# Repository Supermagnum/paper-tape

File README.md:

# Paper Tape Reader

**Repository:** [github.com/Supermagnum/paper-tape](https://github.com/Supermagnum/paper-tape)

Design and documentation by [Jürgen Müller / e-basteln](https://e-basteln.de/computing/papertape/overview/). This repository contains the firmware, PCB design files, and manufacturing data for the manual optical paper tape reader described on the [e-basteln Paper Tape Reader pages](https://e-basteln.de/computing/papertape/overview/).

PCB files converted to KiCad. Note that the main board and included template PCBs use **1.6 mm** thickness. The Gerber files in `gerbers/papertape_spacer/` are for the **1.6 mm templates** (identifiable by their larger aperture holes), used as alignment guides during assembly.

The actual **spacers** (2× 1.2 mm thick) are **not included as Gerber files** and must be made separately. The main board and spacer templates also require **different PCB thicknesses** and must be ordered as **separate jobs** from your PCB manufacturer. Both 1.6 mm and 1.2 mm are standard thickness options at JLCPCB and PCBWay, with a minimum order of 5 pieces each.

The material of the spacers is not important, they just have to be light-tight. Options include 3D printing in black filament, or cutting from 1.2 mm black acrylic or similar opaque material. Use the 1.6 mm template PCB as a guide when making them. Make 2× spacers, for a total thickness of 2.4 mm.

## Table of Contents

- [Overview](#overview)
- [Using the Reader](#using-the-reader)
  - [Capturing tape data](#capturing-tape-data)
  - [After capture](#after-capture)
  - [Archiving captures on Codeberg](#archiving-captures-on-codeberg)
    - [Creating a Codeberg account](#creating-a-codeberg-account)
    - [Creating a repository](#creating-a-repository)
    - [Uploading files via the web interface](#uploading-files-via-the-web-interface)
- [LEDs](#leds)
- [Calibration](#calibration)
- [Jumpers](#jumpers)
- [Serial Output](#serial-output)
- [Building the Reader](#building-the-reader)
  - [Builder's Hints](#builders-hints)
    - [Sourcing the parts](#sourcing-the-parts)
    - [Preparing the PCBs](#preparing-the-pcbs)
    - [Populating components](#populating-components)
    - [Populating sockets and pins](#populating-sockets-and-pins)
    - [Programming the Pro Micro](#programming-the-pro-micro)
- [Design Approach](#design-approach)
- [The Sales Pitch](#the-sales-pitch)
- [Where to Find Files](#where-to-find-files)
- [Design Files](#design-files)
  - [Changes in this repository](#changes-in-this-repository)

## Overview

This little manual paper tape reader is easy to build and operate. It connects to any modern computer via USB, and performs well with all kinds of 5 to 8 bit paper tape, including translucent paper materials. To compensate for sensor tolerances and adjust to different paper types, it can automatically calibrate its optical sensors.

The paper tape reader is controlled by an Arduino Pro Micro. Punched holes are detected optically, via analog inputs to the Arduino and automatic thresholding in software.

Optical readers for punched paper tape have been used since the 1940s; the one developed in 1942 for the British Heath Robinson deciphering machine was probably among the earliest. Non-motorized optical readers, where the tape is pulled through by hand, became popular with early computer amateurs in the 1970s. Oliver Audio Engineering launched the OP80A as a kit or complete unit in 1976; a replica is still commercially available today. And to this day, amateurs interested in the old paper tape format occasionally build their own optical readers.

Operate the reader handheld or mounted to a base plate. Tape is pulled through manually, at up to 1 meter/second feed rate.

The two main modules are the phototransistor detector (left) and the LED illuminator (right). The Arduino sits on top of the detector module. Only two power connections go to the illuminator.

All chassis parts are made from PCB material: Circuit boards for phototransistors and LEDs, masks to precisely define the illumination and detection apertures, and light-tight spacers.

## Using the Reader

To use the paper tape reader, simply connect it to a Windows 10, Linux or Mac OS computer via USB. The reader should automatically register as a USB CDC device (communication device class, a virtual serial port).

Start a terminal program of your choice and select the right (virtual) serial port. No need to set the baud rate etc., since no physical serial port is involved. The reader will start sending data as soon as you pull paper tape through.

Before the first operation, or when switching to a new type of paper tape with very different transparency, calibrate the reader as described below.

### Capturing tape data

Open the serial port and save the received contents to a `.txt` file with **no processing**. Capture the raw bytes exactly as received, save as plain text, and do not strip or convert anything. This means:

- No parity bit masking
- No line ending conversion
- No stripping of leader/trailer nulls
- No interpretation of control characters

This preserves everything and keeps your options open for later analysis.

**Linux:** find the device (often `/dev/ttyACM0` or `/dev/ttyUSB0`), then capture directly:

```bash
stty -F /dev/ttyACM0 raw -echo
cat /dev/ttyACM0 > 20250627_tape_001.txt
```

Press Ctrl+C when the tape has passed through. Do not pipe through tools that alter line endings or encoding.

**macOS:** same approach using the device under `/dev/tty.usb*` or `/dev/cu.usb*`.

**Windows:** use a terminal that can log raw serial data to a file without translation (for example PuTTY with "All session output" logging, or a dedicated serial capture tool). Disable any "local echo", line editing, or automatic CR/LF conversion in the terminal settings.

A good naming convention helps since you do not know the content yet:

```
YYYYMMDD_tape_001.txt
```

If you are digitizing a collection, this lets you track what you have read and when, and rename files later once you figure out what each tape contains.

### After capture

Once you have a faithful raw capture, you can:

- Open it in a hex editor to inspect the raw bytes and identify the format
- Run `file tape_001.txt` on Linux, which will attempt to auto-detect the content type
- Look for recognizable patterns such as keywords (`PROGRAM`, `BEGIN`, `MOV`, `LDA`, etc.) that identify the language
- Check the [bitsavers.org](https://bitsavers.org/) archive, which has a large collection of documented paper tape formats for comparison

The key principle is: **capture first, identify later**. You can always convert a faithful raw capture, but you cannot recover data that was thrown away during capture.

### Archiving captures on Codeberg

If you want to share digitized tapes with the retrocomputing community, [Codeberg](https://codeberg.org/) is a good place to host them. Codeberg is independently operated by [Codeberg e.V.](https://codeberg.org/Codeberg/Association), a non-profit association registered in Berlin, Germany. It is community driven, privacy focused, and runs on the open-source [Forgejo](https://forgejo.org/) platform under German and EU law (GDPR). For archival work, that means no commercial pressure to monetize the platform, stronger data protection than many US-hosted services, and a community that tends to appreciate preservation projects.

#### Creating a Codeberg account

1. Open [codeberg.org](https://codeberg.org/) in your browser.
2. Click **Register** in the top-right corner.
3. Choose a username, enter your email address, and set a password.
4. Complete the registration form and submit it.
5. Check your email for a confirmation link from Codeberg and click it to activate the account.
6. Sign in with your new username and password.

#### Creating a repository

1. After signing in, click the **+** icon in the top-right corner and select **New Repository**.
   Alternatively, open your dashboard and click **New Repository** there.
2. Fill in the repository details:
   - **Owner:** your username (or an organization, if you belong to one)
   - **Repository name:** for example `paper-tape-archive`
   - **Description:** short summary, e.g. "Digitized paper tape captures"
   - **Visibility:** choose **Public** if you want others to browse and clone the archive
   - **Initialize repository:** leave **Add a README file** unchecked if you plan to upload your own files immediately; check it if you want Codeberg to create an empty starter `README.md` for you
3. Click **Create Repository**.

You now have an empty repository ready for uploads.

#### Uploading files via the web interface

Codeberg's web interface lets you add files without installing Git on your computer. This works well for small archives and individual tape captures.

**Upload the first files to an empty repository:**

1. Open your new repository in the browser.
2. If the repository is completely empty, Codeberg shows an **Upload file** option on the landing page. Click it.
   If the repository already has files, go to the **Code** tab, click the **+** drop-down next to the path bar, and choose **Upload file**.
3. Drag and drop files into the upload area, or click to browse your computer.
4. In the **Commit message** field, enter a short note such as `Add initial archive structure`.
5. Optionally expand **Commit options** and choose whether to commit directly to the default branch (usually `main`).
6. Click **Commit changes**.

**Add a tape capture in a subdirectory:**

1. Navigate to the folder where the tape should live, for example `tapes/unknown/20250627_tape_001/`.
   To create a new folder path, type the full path into the filename field when uploading, for example:
   `tapes/unknown/20250627_tape_001/tape_001.txt`
   Codeberg creates any missing directories automatically.
2. Upload the raw capture file (`tape_001.txt`) and the tape's `README.md` (create the README in the web editor if you prefer).
3. Enter a commit message such as `Add tape 001 capture from 2025-06-27`.
4. Click **Commit changes**.

**Create or edit a README in the browser:**

1. On the **Code** tab, click the **+** drop-down and choose **New file**.
2. Enter the path, for example `tapes/unknown/20250627_tape_001/README.md`.
3. Type or paste the README content into the editor.
4. Add a commit message and click **Commit changes**.

Repeat for each new tape. Once you have several captures, consider organizing them using the directory structure below.

Suggested directory structure:

```
paper-tape-archive/
├── README.md                    # Project description, how to contribute
├── FORMATS.md                   # Notes on identified tape formats
│
└── tapes/
    ├── unknown/                 # Tapes not yet identified
    │   └── 19700101_tape_001/
    │       ├── README.md        # Date, physical condition, likely source
    │       ├── tape_001.txt     # Raw capture
    │       └── tape_001.bin     # Raw binary if needed
    │
    ├── assembler/
    │   └── 19780315_tape_002/
    │       ├── README.md
    │       └── tape_002.txt
    │
    ├── basic/
    ├── fortran/
    ├── pascal/
    └── other/
```

Each tape's `README.md` should contain something like:

```markdown
# Tape 001

- **Date captured:** 2025-06-27
- **Capture device:** Paper Tape Reader (github.com/Supermagnum/paper-tape)
- **Likely source:** [e.g. university surplus, estate sale, donated collection]
- **Physical condition:** [good/fair/poor, any damage notes]
- **Tape width:** [5/7/8 bit]
- **Identified format:** unknown
- **Notes:** [anything else relevant]
```

Move tapes from `unknown/` into `assembler/`, `basic/`, `fortran/`, or another category once the format is identified, and update `FORMATS.md` with what you learned.

## LEDs

Two LEDs on the Pro Micro board are used to signal the operating status. They are labelled on the detector PCB:

- **FEED** flashes once for every valid feed hole detected during operation and calibration.
- **CAL** indicates that calibration mode is active, or that a calibration is recommended.

| CAL indication | Meaning |
|----------------|---------|
| Steady ON | Calibration mode is active |
| Flashing, 1 Hz | Waiting for user to start calibration (press CAL button), or for 10 s timeout |
| Flashing, 10 Hz | Error during the calibration process |
| ON in read mode | Invalid brightness levels have been read (no clear high or low). Recalibration is recommended. |

## Calibration

1. Press **CAL** once to view the current calibration. Current calibration values are printed via USB, the CAL LED blinks at 1 Hz.
2. Press **CAL** again within 10 seconds to enter calibration mode. You will be prompted via a USB message to start feeding tape, the CAL LED turns on.
3. Feed tape, beginning within 10 seconds. Approximately 30 cm of sample tape are required. Ideally all data bits should be exercised in the sample, but if no significant contrast is detected for a data channel, averaged thresholds from the other channels will be used. The CAL LED stays on, the FEED LED begins to flash when valid feed holes are seen.
4. Calibration automatically ends when enough sample tape has been processed, or when one of the 10 second timeouts mentioned above is reached. Results and final status are printed via USB; errors are also signaled by rapid flashing of the CAL LED for 1 second. The CAL LED is then switched off.

## Jumpers

Three different tape widths can be set via jumpers. Setting them properly is recommended to avoid "CAL" indications from invalid detection levels at the tape edges, and to mask invalid bits from the output bytes.

| Tape width | Tape/bit placement | Jumper settings |
|------------|-------------------|-----------------|
| 8 bit | 76543.210 | 5BIT=open, TST=open |
| 7 bit | - 6543.210 | 5BIT=set, TST=set |
| 5 bit | - - 432.10 - | 5BIT=set, TST=open |

Note that the 7-bit setting is only required for the rather uncommon type of paper tape which is physically only seven rows wide. For this narrower tape, the 7-bit setting masks out any invalid readings from the eighth detector (which looks just at the tape edge). The common 1" wide tape can be read in the 8-bit setting, no matter whether seven or eight rows of holes are actually punched on it.

Setting only the **TST** jumper will activate test mode, where the raw ADC readings from all 9 channels are printed on the output in an endless loop. From left to right, bits 0 to 7 are displayed, followed by the feedhole signal on the far right. A high value, up to 255, indicates high brightness.

The **INV** jumper will set the reader to use inverted intensity thresholds, i.e. a logical '1' or an active feed track pulse are signaled by a dark light level. This is useful for reading paper tapes which have not been punched, but printed on thin paper, for demonstrations or tests where real paper tape and a punch device are not available. Since the light levels will be lower in this case, it is recommended to replace the resistor array RN1 by a 22 kOhm array.

**TX** is not a jumper, but a serial output. This can optionally be used to connect legacy equipment. Please see the Serial Output section below for details.

## Serial Output

Normally, the USB port is used to interface the tape reader to a modern computer. If you want to read paper tapes into a vintage computer without a USB port, you can use the TX pin on the jumper row which sends "real" serial data.

- All data read from paper tape will be transmitted as an asynchronous serial data stream: 9600 baud, 8 data bits, no parity, 1 stop bit. Voltage levels are positive: A logical '1' (which is also present at rest) is represented by +5 V, a logical '0' (which is also the start bit of each character) by 0 V.
- The baud rate can only be changed by editing the Arduino source code. Look for the `SERIAL_INIT()` call; this is a macro which goes back to `Serial1.begin()` and accepts the baud rate as a parameter.
- To connect to computers with classic RS-232 ports, an external level converter to +/-5 V .. +/-12 V is needed. These are available off-the-shelf or as a kit. They also invert the signal polarity, making logical '1' a negative voltage as defined in the RS-232 standard.
- To provide 5 V power to the level converter, you can omit capacitor C1 and install two more posts (pins) in that position. The outermost pin has +5 V, the next one is another GND pin (see the pin table below). You can also power the paper tape reader via this pin if you do not want to use the USB port.
- Neither calibration data and prompts nor the raw ADC readings in TST mode will be transmitted via this output. This is deliberate; the idea is to use a modern PC to set up the reader, and not bother the vintage system with these setup data.

Summary of all pins on the jumper row and their functions:

| Pin | Function |
|-----|----------|
| +5 V | Power, e.g. for optional external RS-232 level converter |
| GND | Ground (0 V) |
| 5BIT | Jumper to GND: 5 bit or 7 bit tape width |
| GND | Ground (0 V) |
| INV | Jumper to GND: Use printed paper tape with dark 'holes' |
| GND | Ground (0 V) |
| TST | Jumper to GND: Test mode, transmit raw ADC readings via USB |
| GND | Ground (0 V) |
| TX | Serial output: TTL level, 9600 8N1 |
| GND | Ground (0 V) |

## Building the Reader

There are no step-by-step illustrated building instructions here. But with the sectional view of the PCB stack below and the following hints the build should be straightforward.

Sectional view of the stack of PCBs which make the chassis, as well as the key electronic components. For clarity, only 5 of the 8 data sensors and LEDs are shown.

### Builder's Hints

#### Sourcing the parts

- The design files for the custom circuit boards are provided in the Design Files section below. You can order the PCBs cheaply from vendors like JLCPCB, PCBWay, Aisler etc. by uploading the zipped Gerber files provided.
- The [PCBWay shared project](https://www.pcbway.com/project/shareproject/paper_tape_reade_0e895082.html) lists all parts needed to build the reader (PCBs and components). The part list is in `docs/papertape_bom_PCBWay Community.csv`.
- While the microcontroller board is commonly called an "Arduino Pro Micro", and is fully compatible with the Arduino development tools, it was not designed by the Arduino company but by Sparkfun. You can purchase the original Sparkfun Pro Micro or one of various cheaper "Pro Micro" or "Arduino Pro Micro" clones available on ebay etc. In either case, be sure to buy the **5 V / 16 MHz** version! The variant operating at 3.3 V and 8 MHz is not suitable for this project.
- A Digikey shopping cart is available for most of the other parts. If you are based in Europe, Reichelt may be a lower-cost alternative supplier (see the bill of materials in the Design Files section below). The Digikey cart contains alternative values for the resistor array (2.7 kOhm or 10 kOhm), in case of major batch variations of the LEDs or photo-transistors. These may not be necessary. To my knowledge, all builds so far have successfully used the standard 4.7 kOhm array.

#### Preparing the PCBs

- The circuit boards and aperture boards for the detector and illumination are all made in one piece, to ensure that holes and milling contours align on all of them. (Probably an unnecessary precaution.) Hence you need to first break these boards apart, roughly clip off the tabs, and then sand the contours smooth. I recommend that you assemble the complete PCB package with screws according to the picture below and then sand it as a package to obtain even contours.
- Please note that the fibers in PCB dust may be harmful. Work outside or in an area where you can contain the dust, and wear a protective mask.

*The stack of PCBs that make the paper tape reader.*

- The aperture hole for the feed track is only 1.2 mm in diameter, matching the feed holes in the paper tape for maximum signal modulation. On both aperture PCBs this hole needs to be drilled out to 1.8 mm to accommodate the LED and phototransistor, as indicated in the silk screen print on the PCB. But do not drill all the way through; this must be drilled as a blind hole, preserving the 1.2 mm optical aperture! Note that extreme care must be exercised in drilling this hole. Use a drill press and/or much care to drill to the right depth. The standard tolerance for a 1.6 mm PCB is ±10%, which means ±0.16 mm. The WP406A10SURDK LED protrudes 1.55 mm up from its body; tolerance is ±0.25 mm, so start with a hole depth of 0.5 mm. Maximum you'd ever need to drill is 1.0 mm, leaving at worst 0.44 mm of wall.

- To create a gap for the paper tape between the two aperture PCBs, two strips of adhesive tape are placed on top of the LED aperture board. This also provides lateral guidance for the paper tape, so you have to decide on a tape width you want to read. (I intend to provide inserts to reduce from 8-bit tape to 7 or 5 bit width, but have not tried this yet.)
- Fix the aperture PCB to the work bench with a bit of adhesive tape, position a short piece of punched paper tape exactly over the apertures as a reference and attach it to the bench as well. Apply two strips of adhesive tape to the PCB, right next to the paper tape, as a spacer and guide. About 200 um should be a good thickness; you may need to stack two layers of electrical tape or similar to get there. With a sharp knife, trim the tape along the PCB contours and cut the holes for screws and power connector.
- To make it easier to introduce the paper tape into the narrow gap later, you can lightly sand the edges of the LED aperture PCB in the space between the two guide tapes. This creates a slight "funnel" for insertion of the paper tape.

*The pre-assembled modules: Phototransistor detector with apertures (left) and LED illuminator with apertures and spacer tape (right). Two sockets and wires provide power to the LEDs.*

#### Populating components

- To populate the LEDs, insert all 9 loosely into the PCB. (Note the correct orientation; the body outline is shown on the silkscreen print.) Put the two spacer PCBs and the aperture PCB on top, wiggle the LEDs into their respective aperture holes, and hold the PCB stack together with screws or adhesive tape. Push the LEDs all the way down into their holes. The feed hole LED will not go quite as far into its blind hole as the other LEDs. Then solder all LEDs.
- Do the same with the phototransistors.
- The LED series resistors (R1 to R5) can be populated as through-hole resistors inside the module. This requires resistors with a diameter less than 2.4 mm, the thickness of the two spacer PCBs. The diameters of through-hole resistors vary by manufacturer. If you cannot find suitably slim through-hole resistors, you can either mount them on the opposite side of the PCB, or you can populate 0603 or 0805 sized SMD resistors on the provided pads.

#### Populating sockets and pins

- For the 5V power connection to the illuminator module, solder a two pin socket to the bottom of the detector board. (Make sure to get it reasonably straight.) Insert two clipped wire ends into the sockets. Provisionally assemble the full PCB stack while guiding the wires through their pads in the illuminator board. Clip wires to length and solder them to the illuminator board.
- You can solder the Arduino Pro Micro permanently to the detector PCB with the square soldering pins provided with most Arduino boards. This will give the lowest-profile package. If that is what you prefer, make sure that the phototransistors and 5V supply socket are soldered before you place the Arduino! Alternatively, use two rows of 1x12 pin sockets for the Arduino. In that case, the standard square pins will not fit, and you need to obtain smaller (turned) pin headers to match the sockets.
- The resistor array RN1 (9 x 4.7 kOhm) can be soldered directly if you only want to read "real", punched paper tape. Be sure to check the orientation; the common pin must be oriented towards the USB jack. If you want to use printed tape in the future, i.e. black dots on translucent paper, you may need to exchange RN1 for a 22 kOhm or 33 kOhm array to give higher light sensitivity. In that case, use a 1x10 pin socket for RN1.

*I opted for sockets for the resistor array (so I can try different values) and the Arduino (in case I need to get to the soldering joints beneath it).*

#### Programming the Pro Micro

- The Pro Micro processor is programmed via the regular Arduino environment, via its Micro USB connection. Please find the source code for the paper tape reader in the Design Files section just below.
- The Pro Micro board description is not pre-installed in the Arduino IDE. The required steps are briefly presented below. There is also a more detailed tutorial from Sparkfun; see the "Installing on Windows" or "Installing on Mac/Linux" sections there. That tutorial also covers manual installation of the serial driver on Windows if it is not available automatically (as it should from Windows 10 onwards).
- First, select **File / Preferences** from the main menu. In the dialog which opens, enter the URL below in the "Additional Board Manager URLs" field. Then select **Tools / Board / Boards Manager** and install the "SparkFun AVR Boards" package.

  ```
  https://raw.githubusercontent.com/sparkfun/Arduino_Boards/master/IDE_Board_Manager/package_sparkfun_index.json
  ```

- Again from the main menu, select **Tools / Processor: ATmega32U4 (5V, 16 MHz)**. It is important to choose the right version! If you accidentally try to program a 5V Pro Micro with the settings for the 3.3V version, you may brick it, requiring a hard reset. Connect the Pro Micro via USB, and set the right COM port via **Tools / Port**. Now you are ready to compile and upload the paper tape reader's software!

## Design Approach

This project takes a slightly different approach than most builds. While I also use LED and phototransistor pairs to detect the presence of holes or paper, and use the feed (sprocket) hole to trigger a read cycle, this reader does not distinguish "zero" from "one" via hardware comparators or Schmitt triggers. Instead, the on-board microcontroller (a Sparkfun/Arduino Pro Micro) reads the phototransistor currents via its analog inputs. This way it can adjust the detection thresholds in software, to compensate for tolerances between the phototransistors and to adjust to different paper materials.

## The Sales Pitch

- **Easy to use.** Just connect it to any modern computer (Windows 10, Mac OS, Linux) via USB, open a terminal program or copy from the serial device to a file, pull through some paper tape, and you are in business. You can calibrate the sensors to difficult-to-read, translucent tape by pushing a button and feeding about 30 cm of test tape. But one calibration handles a wide range of paper types, and stays resident in EEPROM memory, so you do not have to calibrate much at all.
- **Easy to build.** Only through-hole electronic components are required. Most mechanical parts consist of pre-fabricated circuit board material; just add four screws and some adhesive tape (which is used as a spacer to guide the paper tape). No hand-selected resistor values to get the sensor switching thresholds just right, since all sensors are calibrated in software. The microcontroller is programmed via USB and the standard Arduino environment.
- **Works pretty well.** Due to the analog sensing and software calibration, the reader handles a wide variety of tape materials robustly, including highly translucent white or yellow paper. It is insensitive to environmental light since the tape and sensors are fully encapsulated. While it is not the fastest reader around, reading speed is probably limited by how fast you can pull the tape through without damaging it: Reading at 1.2 meter/second (500 characters per second) should not be a problem.

## Where to Find Files

Clone or download this repository from [github.com/Supermagnum/paper-tape](https://github.com/Supermagnum/paper-tape).

```
paper-tape/
├── README.md                      # This manual
├── Paper_Tape_Reader.ino          # Arduino firmware
├── papertape_pcb.sch              # Original Eagle schematic
├── papertape_pcb.brd              # Original Eagle main PCB
├── papertape_spacer.brd           # Original Eagle spacer PCB
├── kicad/
│   ├── papertape_pcb.kicad_pcb    # Main PCB (KiCad, converted from Eagle)
│   ├── papertape_pcb.kicad_sch    # KiCad schematic
│   ├── papertape_pcb.kicad_pro    # KiCad project file
│   ├── papertape_spacer.kicad_pcb # Spacer PCB (KiCad)
│   └── papertape_panel.kicad_pcb  # Panel: main + 4x spacer (2x2, 2 mm gap)
├── gerbers/
│   ├── papertape_pcb/             # Gerbers for main board
│   ├── papertape_spacer/          # Gerbers for spacer board
│   └── papertape_panel/           # Gerbers for combined panel
├── docs/
│   ├── papertape_bom.pdf          # Bill of materials (original)
│   ├── papertape_bom.csv          # Bill of materials with manufacturer MPNs
│   ├── papertape_bom_PCBWay Community.csv  # Part list for PCBWay shared project
│   ├── papertape_all.pdf          # Full design documentation (PDF)
│   └── Paper_Tape_Template.xlsx   # Paper tape template
└── images/                        # Build photos and PCB stack diagram
    ├── ls_complete.jpg
    ├── ls_two_parts.jpg
    ├── ls_parts.jpg
    └── pcb_stack.png
```

Order PCBs and components from the [PCBWay shared project](https://www.pcbway.com/project/shareproject/paper_tape_reade_0e895082.html), which includes all parts needed; see `docs/papertape_bom_PCBWay Community.csv` for the part list. Alternatively, upload the Gerber files from `gerbers/papertape_pcb/` and `gerbers/papertape_spacer/`, or use `gerbers/papertape_panel/` for the combined panel layout. Both PCBWay and JLCPCB have a minimum order of 5 sets.

## Design Files

| File / directory | Description |
|------------------|-------------|
| `Paper_Tape_Reader.ino` | Arduino firmware source code |
| `kicad/papertape_pcb.kicad_pcb` | Main detector/illuminator PCB (KiCad) |
| `kicad/papertape_spacer.kicad_pcb` | Spacer PCB (KiCad) |
| `kicad/papertape_panel.kicad_pcb` | Combined panel: main board + 4x spacer (2x2 grid, 2 mm routing gap) |
| `kicad/papertape_pcb.kicad_sch` | KiCad schematic |
| `gerbers/papertape_pcb/` | Gerber + drill files for main board |
| `gerbers/papertape_spacer/` | Gerber + drill files for spacer |
| `gerbers/papertape_panel/` | Gerber + drill files for panel |
| `docs/papertape_bom.pdf` | Bill of materials (original PDF) |
| `docs/papertape_bom.csv` | Bill of materials with manufacturer part numbers (CSV) |
| `docs/papertape_bom_PCBWay Community.csv` | Part list for the PCBWay shared project (all parts needed) |
| `papertape_pcb.sch`, `papertape_pcb.brd` | Original Eagle design files |
| `papertape_spacer.brd` | Original Eagle spacer board |

### Changes in this repository

The original Eagle designs from [e-basteln](https://e-basteln.de/computing/papertape/overview/) have been converted to KiCad (`papertape_pcb.kicad_pcb`, `papertape_spacer.kicad_pcb`). During conversion, pre-drill holes were added to the PCB files where required for blind-milled feed-track apertures and other mechanical features that are not represented in the standard drill file alone.

For panelised manufacturing, the main PCB and spacer boards are also combined in `kicad/papertape_panel.kicad_pcb`: one main board at its original position, plus four spacer instances in a 2x2 grid to the right with a 2 mm routed gap between boards. Each panel is one complete set; PCBWay and JLCPCB both require a minimum order of 5 sets.

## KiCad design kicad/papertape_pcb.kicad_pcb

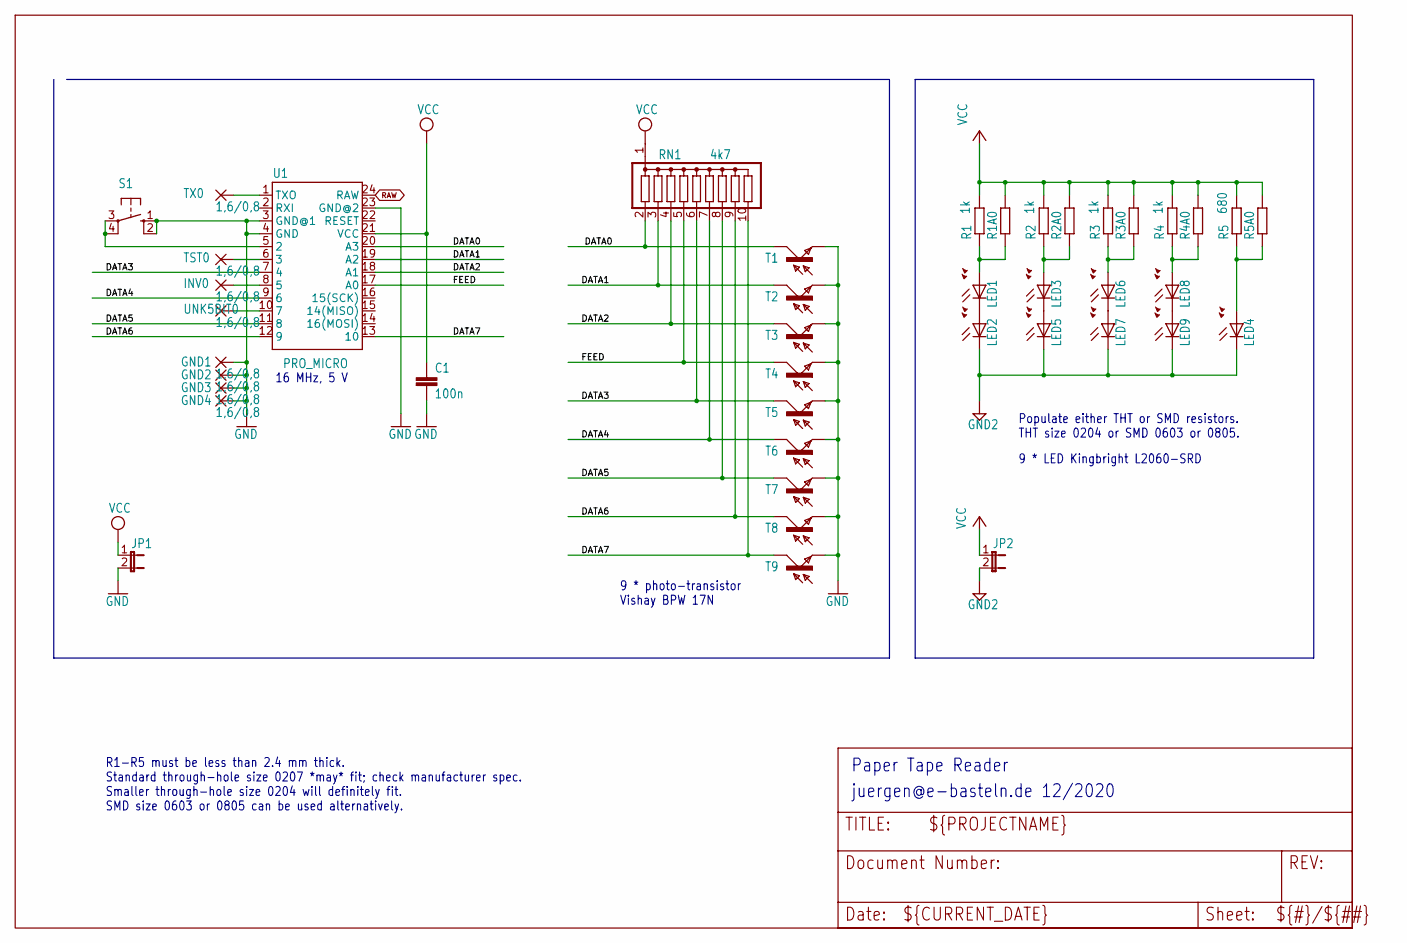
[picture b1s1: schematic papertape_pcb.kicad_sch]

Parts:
C1: 100n; C025-024X044
GND1, GND2, GND3, GND4: 1,6/0,8; 1,6_0,8
INV0: 1,6/0,8; 1,6_0,8
JP1, JP2: JP1E; JP1
LED1, LED2, LED3, LED4, LED5, LED6, LED7, LED8, LED9: LEDLED1MM8; LED1MM8
R1, R2, R3, R4: 1k; 0204_7
R1A0, R2A0, R3A0, R4A0, R5A0: R-EU_R0805; R0805
R5: 680; 0204_7
RN1: 4k7; SIL10
S1: 10-XX; B3F-10XX
T1, T2, T3, T4, T5, T6, T7, T8, T9: BPW17N
TST0: 1,6/0,8; 1,6_0,8
TX0: 1,6/0,8; 1,6_0,8
U1: PRO_MICRO; SPARKFUN_PRO_MICRO
UNK5BIT0: 1,6/0,8; 1,6_0,8

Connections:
DATA0: RN1.2, T1.C, U1.20 (A3)
DATA1: RN1.3, T2.C, U1.19 (A2)
DATA2: RN1.4, T3.C, U1.18 (A1)
DATA3: RN1.6, T5.C, U1.7 (4)
DATA4: RN1.7, T6.C, U1.9 (6)
DATA5: RN1.8, T7.C, U1.11 (8)
DATA6: RN1.9, T8.C, U1.12 (9)
DATA7: RN1.10, T9.C, U1.13 (10)
FEED: RN1.5, T4.C, U1.17 (A0)
GND: C1.2, GND1.1, GND2.1, GND3.1, GND4.1, JP1.2, S1.1 (S), S1.2 (S1), T1.E, T2.E, T3.E, T4.E, T5.E, T6.E, T7.E, T8.E, T9.E, U1.3 (GND@1), U1.4 (GND), U1.23 (GND@2)
GND2: JP2.2, LED2.K (C), LED4.K (C), LED5.K (C), LED7.K (C), LED9.K (C)
unnamed: LED1.K (C), LED2.A
unnamed: LED3.K (C), LED5.A
unnamed: LED6.K (C), LED7.A
unnamed: LED8.K (C), LED9.A
unnamed: INV0.1, U1.8 (5)
unnamed: TST0.1, U1.6 (3)
unnamed: LED4.A, R5.1, R5A0.1
unnamed: TX0.1, U1.1 (TXO)
unnamed: U1.10 (7), UNK5BIT0.1
unnamed: S1.3, S1.4 (P1), U1.5 (2)
unnamed: LED1.A, R1.1, R1A0.1
unnamed: LED3.A, R2.1, R2A0.1
unnamed: LED6.A, R3.1, R3A0.1
unnamed: LED8.A, R4.1, R4A0.1
RAW: U1.24 (RAW)

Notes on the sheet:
juergen@e-basteln.de 12/2020
9 * photo-transistor Vishay BPW 17N
9 * LED Kingbright L2060-SRD
16 MHz, 5 V
Paper Tape Reader
Populate either THT or SMD resistors. THT size 0204 or SMD 0603 or 0805.
R1-R5 must be less than 2.4 mm thick. Standard through-hole size 0207 *may* fit; check manufacturer spec. Smaller through-hole size 0204 will definitely fit. SMD size 0603 or 0805 can be used alternatively.

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
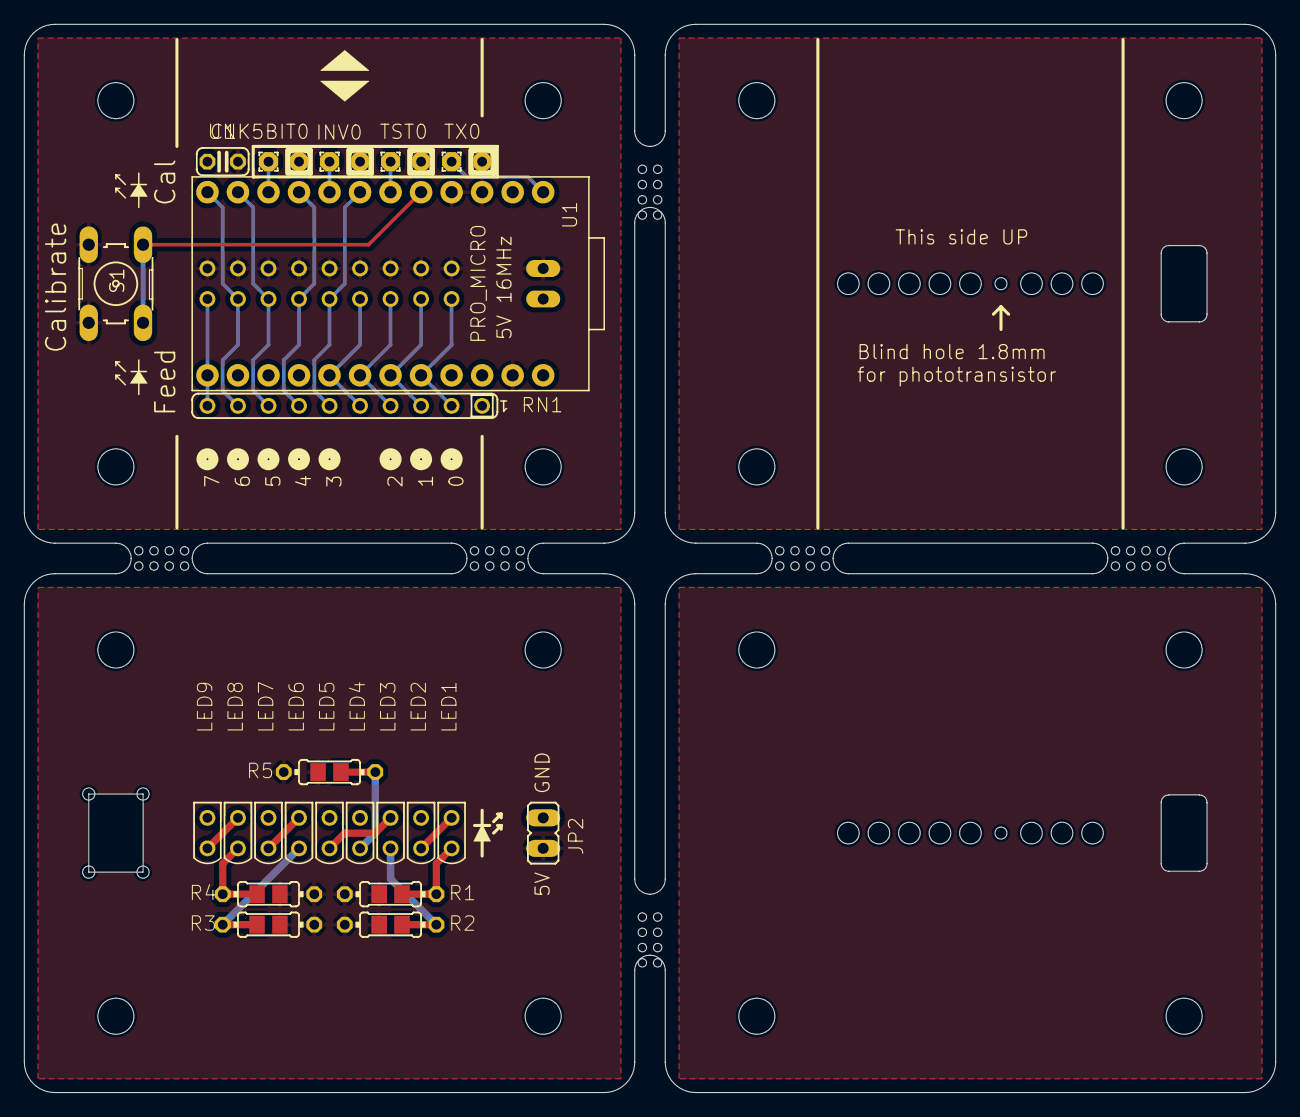
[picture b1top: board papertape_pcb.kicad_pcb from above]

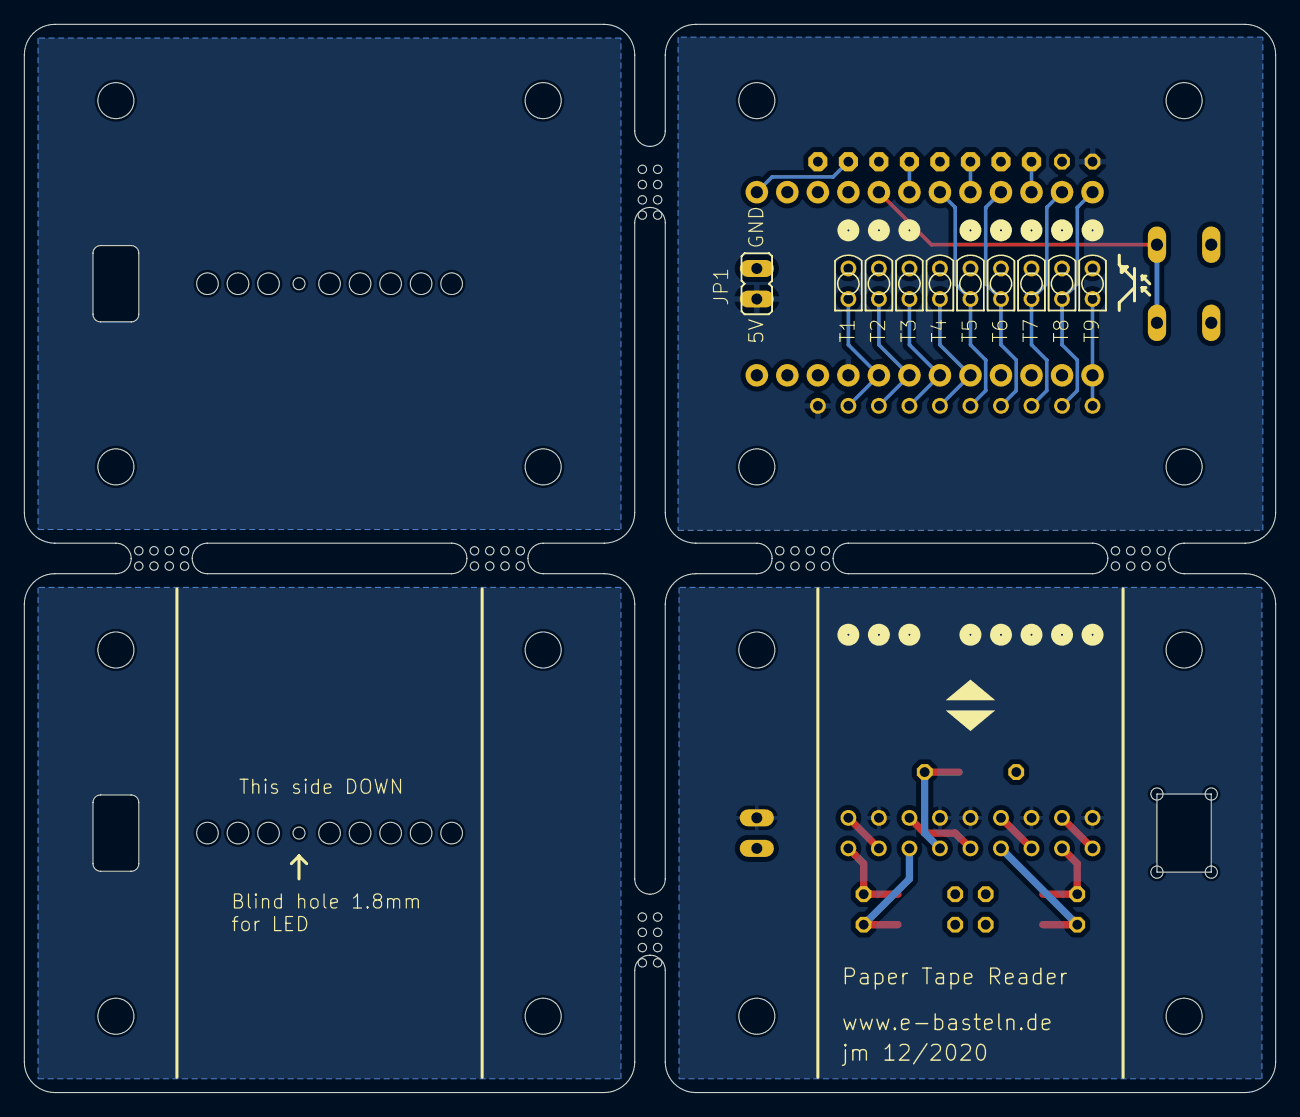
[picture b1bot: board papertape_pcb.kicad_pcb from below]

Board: 2 copper layers, 104.1 x 88.9 mm, 128 parts (10 on the bottom side), 27 nets.

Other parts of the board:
UNK_HOLE_0: dummyfp0
UNK_HOLE_1: dummyfp1
UNK_HOLE_2: dummyfp2
UNK_HOLE_3: dummyfp3
UNK_HOLE_4: dummyfp4
UNK_HOLE_5: dummyfp5
UNK_HOLE_6: dummyfp6
UNK_HOLE_7: dummyfp7
UNK_HOLE_8: dummyfp8
UNK_HOLE_9: dummyfp9
UNK_HOLE_10: dummyfp10
UNK_HOLE_11: dummyfp11
UNK_HOLE_12: dummyfp12
UNK_HOLE_13: dummyfp13
UNK_HOLE_14: dummyfp14
UNK_HOLE_15: dummyfp15
UNK_HOLE_16: dummyfp16
UNK_HOLE_17: dummyfp17
UNK_HOLE_18: dummyfp18
UNK_HOLE_19: dummyfp19
UNK_HOLE_20: dummyfp20
UNK_HOLE_21: dummyfp21
UNK_HOLE_22: dummyfp22
UNK_HOLE_23: dummyfp23
UNK_HOLE_24: dummyfp24
UNK_HOLE_25: dummyfp25
UNK_HOLE_26: dummyfp26
UNK_HOLE_27: dummyfp27
UNK_HOLE_28: dummyfp28
UNK_HOLE_29: dummyfp29
UNK_HOLE_30: dummyfp30
UNK_HOLE_31: dummyfp31
UNK_HOLE_32: dummyfp32
UNK_HOLE_33: dummyfp33
UNK_HOLE_34: dummyfp34
UNK_HOLE_35: dummyfp35
UNK_HOLE_36: dummyfp36
UNK_HOLE_37: dummyfp37
UNK_HOLE_38: dummyfp38
UNK_HOLE_39: dummyfp39
UNK_HOLE_40: dummyfp40
UNK_HOLE_41: dummyfp41
UNK_HOLE_42: dummyfp42
UNK_HOLE_43: dummyfp43
UNK_HOLE_44: dummyfp44
UNK_HOLE_45: dummyfp45
UNK_HOLE_46: dummyfp46
UNK_HOLE_47: dummyfp47
UNK_HOLE_48: dummyfp48
UNK_HOLE_49: dummyfp49
UNK_HOLE_50: dummyfp50
UNK_HOLE_51: dummyfp51
UNK_HOLE_52: dummyfp52
UNK_HOLE_53: dummyfp53
UNK_HOLE_54: dummyfp54
UNK_HOLE_55: dummyfp55
UNK_HOLE_56: dummyfp56
UNK_HOLE_57: dummyfp57
UNK_HOLE_58: dummyfp58
UNK_HOLE_59: dummyfp59
UNK_HOLE_60: dummyfp60
UNK_HOLE_61: dummyfp61
UNK_HOLE_62: dummyfp62
UNK_HOLE_63: dummyfp63
UNK_HOLE_64, UNK_HOLE_65, UNK_HOLE_66, UNK_HOLE_67: dummyfp_cutout
UNK_HOLE_68: dummyfp_predrill1
UNK_HOLE_69: dummyfp_predrill2
UNK_HOLE_70: dummyfp_predrill3
UNK_HOLE_71: dummyfp_predrill4
UNK_HOLE_72: dummyfp_predrill5
UNK_HOLE_73: dummyfp_predrill6
UNK_HOLE_74: dummyfp_predrill7
UNK_HOLE_75: dummyfp_predrill8
UNK_HOLE_76: dummyfp_predrill9
UNK_HOLE_77: dummyfp_predrill10
UNK_HOLE_78: dummyfp_predrill11
UNK_HOLE_79: dummyfp_predrill12
UNK_HOLE_80: dummyfp_predrill13
UNK_HOLE_81: dummyfp_predrill14
UNK_HOLE_82: dummyfp_predrill15
UNK_HOLE_83: dummyfp_predrill16
UNK_HOLE_84: dummyfp_predrill17
UNK_HOLE_85: dummyfp_predrill18

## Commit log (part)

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2026-06-11 Update README with KiCad conversion details
    Converted Eagle designs to KiCad and merged spacer boards into main PCB file.
2026-06-11 Enhance README with detailed project information
    Updated README to include additional details about the paper tape reader, including design files and assembly instructions.
2026-06-11 Revise README with enhanced project details
    Updated README to include additional details about PCB specifications, design approach, and building instructions.
2026-06-11 Fixed hole sizes.
2026-06-11 Updated kicad files.
2026-06-11 Enhance README with detailed assembly and design info
    Updated README to include additional details on PCB specifications, assembly instructions, and design files.
2026-06-26 Revise README for clarity and additional information
    Updated README to include additional details about PCB specifications, assembly instructions, and design files.
